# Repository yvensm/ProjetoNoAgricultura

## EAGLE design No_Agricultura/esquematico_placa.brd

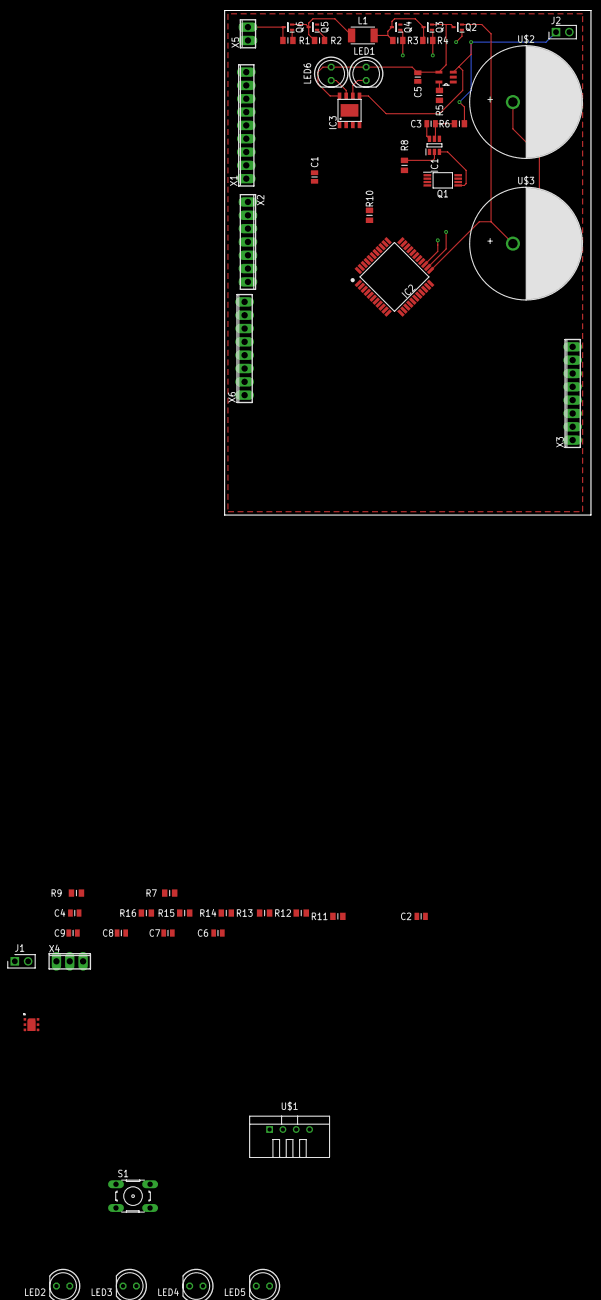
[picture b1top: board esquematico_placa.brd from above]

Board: 2 copper layers, 69.8 x 96.2 mm, 55 parts (0 on the bottom side), 57 nets.

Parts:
C1: 10uF; CAPC2012X70N
C2: 10pF 25V; CAPC2012X70N
C3, C4: 0.1uF; CAPC2012X70N
C5, C6: 4.7 uF 16V; CAPC2012X70N
C7, C8, C9: 0.1uF 20V; CAPC2012X70N
IC1: DW01-P; SOT95P280X135-6N
IC2: PIC18F45K80; QFP80P1200X1200X120-44N
IC3: TP4056; SOP-8
J1, J2: 68001-202HLF; HDRV2W90P0X254_1X2_508X241X854
L1: INDM4532X320N
LED1, LED2, LED3, LED4, LED5, LED6: LED5MM
MCP: MCP73832T; SOT95P300X145-5N
Q1: FS8205A; SOP65P640X120-8N
Q2, Q3, Q4, Q5, Q6: SOT50P160X90-3N
R1, R2, R3, R4: 1M R; RESC2012X70N
R5: 2K R; RESC2012X70N
R6, R7, R8, R9: 1K R; RESC2012X70N
R10: 1.2K R; RESC2012X70N
R11, R12: 10K R; RESC2012X70N
R13, R14, R15, R16: 100 R; RESC2012X70N
S1: RESET; B3F-10XX
U1: HTU21D; QFN100P300X300X100-7N
U$1: TEMP-HUM-SENSOR-DHT22
U$2, U$3: 1F x 2,5 V; KW-5R5C105-R
X1: 9POL254
X2: 7POL254
X3, X6: 8POL254
X4: 3POL254
X5: INPUT; 2POL254

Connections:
AN: IC2.26, X4.1
BATSTAT: IC2.25, MCP.1
CE: IC2.35, X3.2
CSN: IC2.36, X3.6
DAT: IC2.32, U$1.2
DATA: IC2.42, R12.2, U1.1, X3.4
EN: IC2.30, R16.2, X2.3
GND: C1.2, C2.2, C4.2, C5.1, C6.1, C7.1, C8.1, C9.1, IC2.6, IC2.29, IC3.1, IC3.3, J2.2, LED2.K, LED3.K, LED4.K, LED5.K, MCP.2, Q1.7, Q4.2, Q5.2, R5.1, R8.2, R10.2, U1.2, U1.PAD, U$1.4, U$2.2, X1.1, X2.2, X3.1, X4.3, X5.1, X6.8
ICSP_CLK_INPUT: IC2.17, J1.1, R14.2
ICSP_DATA_INPUT: IC2.16, J1.2, R15.2
IN+: Q6.3, R1.2, X5.2
IRC: IC2.31, X3.8
unnamed: L1.1, Q5.3, Q6.2, R2.2
unnamed: L1.2, Q3.3, Q4.3, R3.2, R4.2
unnamed: LED2.A, R13.1
unnamed: MCP.5, R5.2
unnamed: LED3.A, R14.1
unnamed: IC3.7, LED6.K
unnamed: IC3.6, LED1.K
unnamed: U$2.1, U$3.2
unnamed: IC3.2, R10.1
unnamed: R7.1, R9.2, S1.1
unnamed: C3.1, IC1.5, R6.1
unnamed: C8.2, S1.3
unnamed: IC1.2, R8.1
unnamed: IC1.3, Q1.5
unnamed: LED4.A, R15.1
unnamed: LED5.A, R16.1
unnamed: IC1.1, Q1.4
OUT+: C1.1, C5.2, IC3.4, IC3.8, LED1.A, LED6.A, MCP.4, Q2.3, Q3.2
RB0: IC2.8, X6.6
RB1: IC2.9, X6.5
RB2: IC2.10, X6.4
RB3: IC2.11, X6.3
RB4: IC2.14, X6.2
RB5: IC2.15, X6.1
RD0: IC2.38, X1.9
RD1: IC2.39, X1.8
RD2: IC2.40, X1.7
RD3: IC2.41, X1.6
RD4: IC2.2, X1.5
RD5: IC2.3, X1.4
RD6: IC2.4, X1.3
RD7: IC2.5, X1.2
RESET: IC2.18, R7.2
RX: IC2.44, X2.4
SCL: IC2.37, R11.1, U1.6, X3.3
SDO: IC2.43, X3.7
SW1: IC2.22, Q6.1, R1.1
SW2: IC2.21, Q5.1, R2.1
SW3: IC2.20, Q4.1, R3.1
SW4: IC2.19, Q3.1, R4.1
SWCAP: IC2.24, Q2.1
TX: IC2.1, X2.5
VBAT: C2.1, C4.1, C6.2, C7.2, C9.2, IC2.7, IC2.28, IC3.5, J2.1, MCP.3, R6.2, R9.1, R11.2, R12.1, R13.2, U1.5, U$1.1, X2.1, X3.5, X4.2, X6.7
VCAP: IC2.23, Q2.2, U$3.1
VSSBAT: C3.2, IC1.6, Q1.2

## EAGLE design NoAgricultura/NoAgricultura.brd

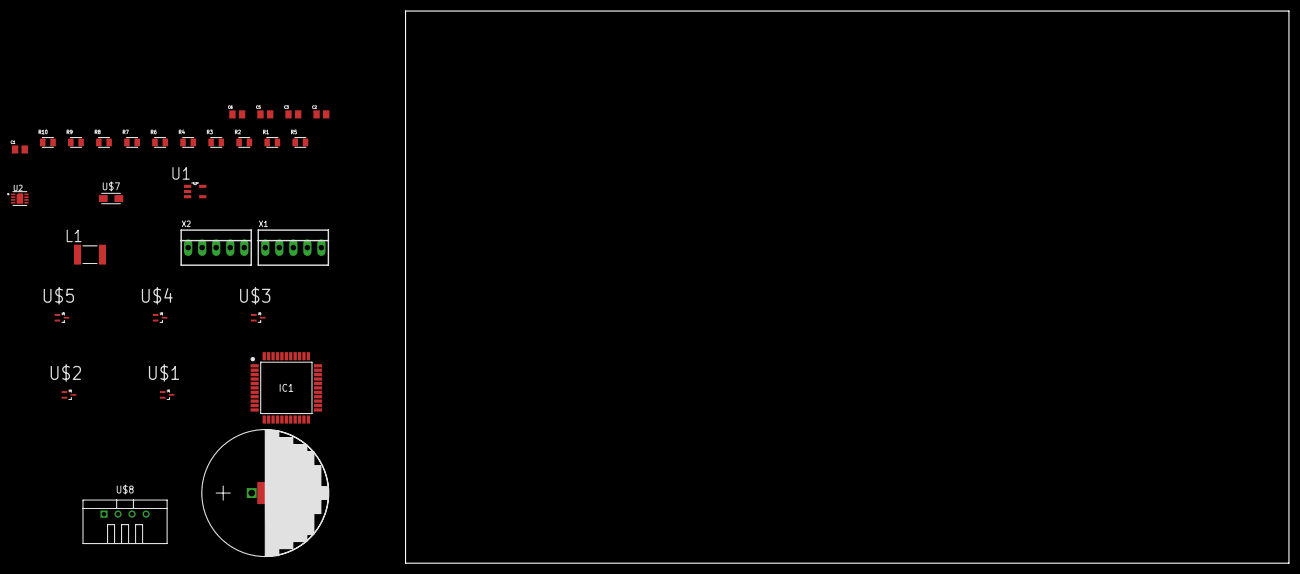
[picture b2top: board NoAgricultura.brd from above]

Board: 2 copper layers, 160.0 x 100.0 mm, 29 parts (0 on the bottom side), 21 nets, no tracks yet.

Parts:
C1, C2, C3, C5, C6: 1uF; CAPC2012X140N
IC1: PIC18F45K80-I_PT; QFP80P1200X1200X120-44N
L1: B82432T1222K; INDC4532X340N
R1, R2, R3, R4: 1M; RESC2012X65N
R5: CRGH0805F392R; RESC2012X65N
R6, R9, R10: 10k; RESC2012X65N
R7: 2K; RESC2012X65N
R8: 100R; RESC2012X65N
U1: MCP73832T-5ACI/OT; SOT95P300X145-5N
U2: SHT31-DIS-B; SON50P250X250X100-9N
U$1, U$2, U$3, U$4, U$5: NTA4151P; SOT50P160X90-3N
U$6: PANASONIC-SCAP-5.5V-0.1F
U$7: CAPTANT-TYPEA; CAPMTANT-TYPEA
U$8: TEMP-HUM-SENSOR-DHT22
X1, X2: 22-23-2051

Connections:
AN0: IC1.19, X2.2
ICSPCLK: IC1.16, X1.5
ICSPDAT: IC1.17, X1.4
IN+: R1.2, U$1.2
MCLR: R8.2, X1.1
unnamed: L1.1, R2.2, U$1.3, U$2.2
unnamed: L1.2, R3.2, R4.2, U$3.2, U$4.2
unnamed: R7.1, U1.5
unnamed: C1.2, R6.1, R8.1
OUT+: R5.2, U$5.2
SCL: IC1.37, R10.2, U2.4, X2.4
SDA: IC1.42, R9.2, U2.1, U$8.2, X2.3
SW1: R1.1, U$1.1
SW2: R2.1, U$2.1
SW3: R3.1, U$4.1
SW4: R4.1, U$3.1
SWCAP: R5.1, U$5.1
VDD: C5.2, C6.2, R9.1, R10.1, U1.4, U2.2, U2.5, U$3.3, U$7.1, U$8.1, X1.2, X2.1
VDD_1: C3.1, IC1.28
VSS: C1.1, C2.1, C2.2, C5.1, C6.1, IC1.6, IC1.7, R7.2, U1.2, U2.7, U2.8, U$2.3, U$4.3, U$7.2, U$8.4, X1.3, X2.5
VSS_1: C3.2, IC1.29

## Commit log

2019-04-22 Criação do Projeto no Eagle
    Criação do projeto no eagle.
2019-04-22 Datasheets e Libs.
    Datasheets e libs dos componentes que serão utilizados no projeto. (Retirados das imagens do diagrama)
2019-04-24 Correção das Libs
    Todas as libs iniciais prontas para uso.
2019-04-25 Alteracao: criacao do simbolo do componente NTA4151P
2019-04-26 Primeira Versão Esquematico
    Primeira versão do esquematico desenhada.
    Correção na lib NTA4151
2019-04-29 Alteracao: Adicionando esquema e bibliotecas Steve
2019-04-29 Capacitores
    4,7uF 16v Tatrium cap: CAPTANT-TYPEA.lbr (LipoCharge Circuit)
    0805 Cap: 0805YC104KA76A.lbr (MCLR PIC Circuit)
2019-04-29 Teste
2019-04-29 Circuito MCLR
    Componentes baixados e circuito montado.
2019-05-02 Adicionando Libs do novo capacitor
2019-05-02 Adicionando novo capacitor ao esquema
2019-05-22 Adicionando supostos datasheets sensor de umidade capacitivo
2019-06-04 Adicionando novos datasheets CI 555
2019-06-24 Sensores de Umidade
    Adicionado circuito dos sensores e de Gravação inCircuit
2019-07-02 adicionando novos controladores da bateria
2019-07-02 Atualizando pasta completa
2019-07-10 Atualizacao placa

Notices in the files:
parts and their libraries:
diy-modules: Released under the Creative Commons Attribution 4.0 International License: http://creativecommons.org/licenses/by/4.0
